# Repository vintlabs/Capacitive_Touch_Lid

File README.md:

# Capacitive_Touch_Lid
Capacitive Touch Button Module for ESP32-Zip

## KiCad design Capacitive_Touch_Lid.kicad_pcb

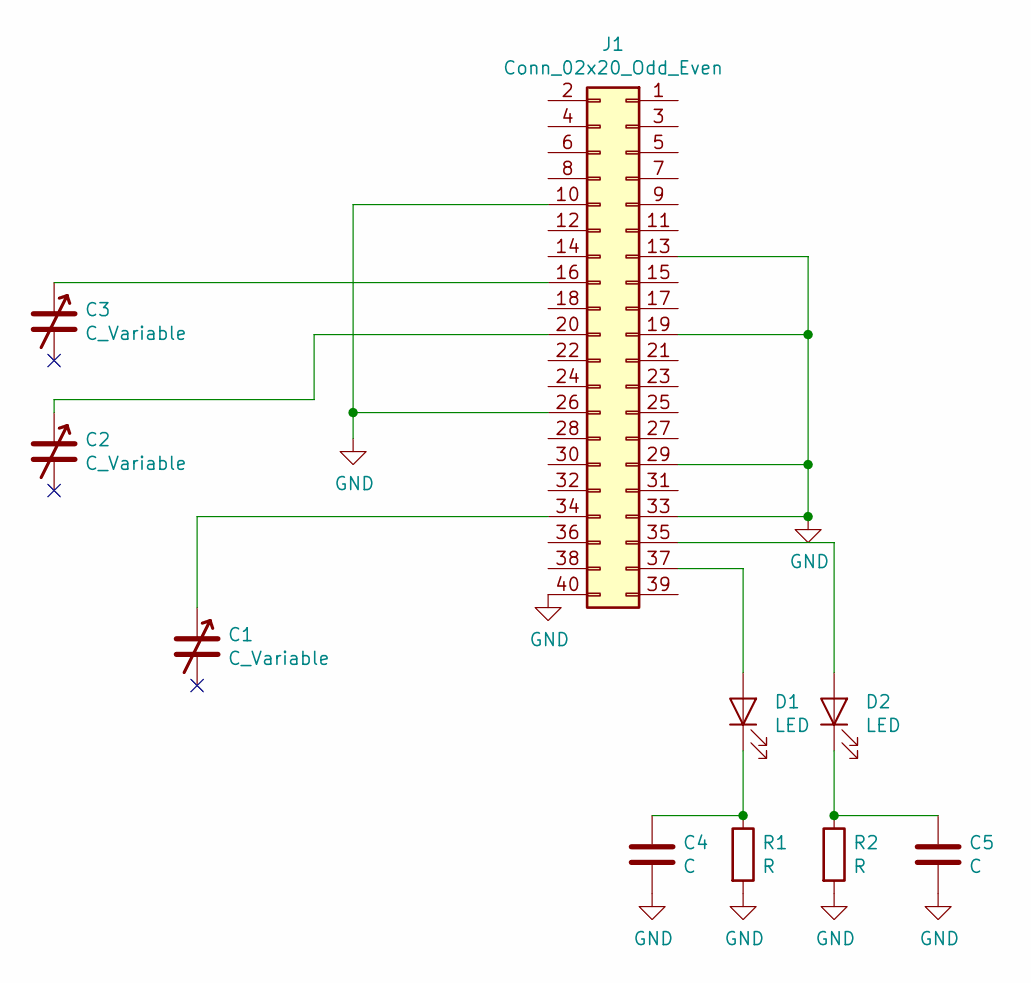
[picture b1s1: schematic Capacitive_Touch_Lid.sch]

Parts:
C1, C2, C3: C_Variable; Round Touch Pad
C4, C5: C; C_0805_2012Metric_Pad1.15x1.40mm_HandSolder
D1, D2: LED; HLMP-Q105 Reverse LED
J1: Conn_02x20_Odd_Even; PinHeader_2x20_P2.54mm_Vertical_SMD
R1, R2: R; R_0805_2012Metric_Pad1.15x1.40mm_HandSolder

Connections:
GND: C4.2, C5.2, J1.10, J1.13, J1.19, J1.26, J1.29, J1.33, J1.40, R1.2, R2.2
unnamed: C1.1, J1.34
unnamed: C2.1, J1.20
unnamed: C3.1, J1.16
unnamed: C4.1, D1.1 (K), R1.1
unnamed: C5.1, D2.1 (K), R2.1
unnamed: D1.2 (A), J1.37
unnamed: D2.2 (A), J1.35

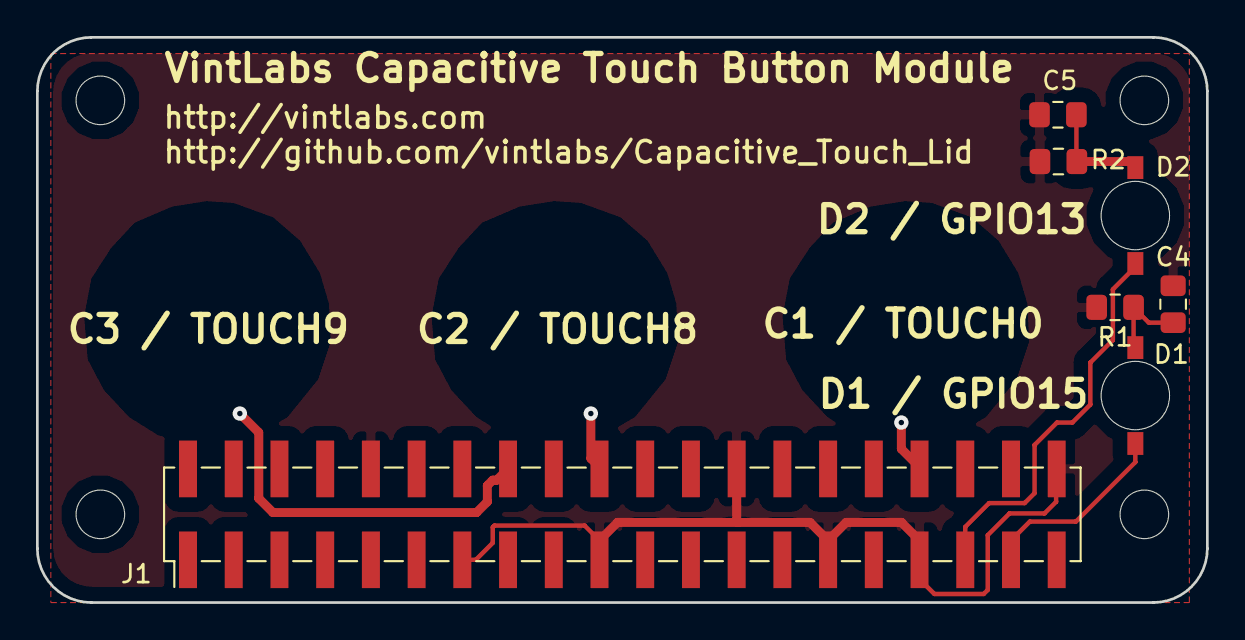
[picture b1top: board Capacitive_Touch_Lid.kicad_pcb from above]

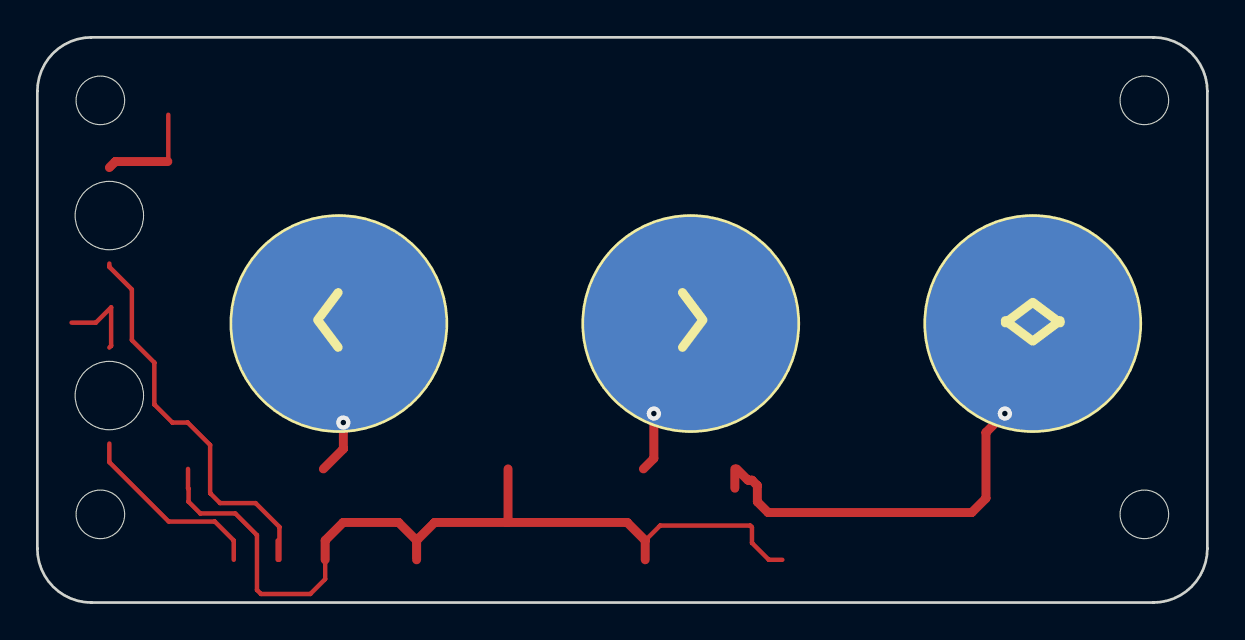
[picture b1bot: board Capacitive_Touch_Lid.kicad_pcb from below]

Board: 2 copper layers, 65.0 x 31.4 mm, 10 parts (3 on the bottom side), 8 nets.

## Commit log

2019-12-28 Initial import
2019-12-31 Flipped board
